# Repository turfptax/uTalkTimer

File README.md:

# uTalkTimer
uTalkTimer: An async ESPNOW-based MicroPython library for efficient discussion management in meetings, featuring speaker time tracking, speech queuing, and voting functionalities.

## Installation and Setup

Follow these instructions to set up the environment and install all required dependencies for the uTalkTimer project.

### Prerequisites

Before you begin, ensure you have MicroPython installed on your ESP32 device. You will also need to install `mpremote` to interact with your MicroPython device from your computer.

#### Installing mpremote

You can install `mpremote` using pip. Open your terminal and run:

```bash
pip install mpremote
```

### Installing Required Libraries

The project depends on the `aioespnow` and `ssd1306` libraries for asynchronous ESPNOW communication and OLED display management, respectively. Follow the steps below to install these libraries on your MicroPython device.

1. **Connect to Your MicroPython Device**:

   First, make sure to close any active IDE connections to the ESP32 micropython device:

   ```bash
   mpremote mip install aioespnow
   mpremote mip install ssd1306
   ```

2. **Verify Libraries**:

   Use thonny or another IDE to varify that the two files are stored in a 'lib' directory with the .mpy extension:

   ```bash
   lib
       aioespnow.mpy
       ssd1306.mpy
   ```
You should see `aioespnow.mpy` and `ssd1306.mpy` listed.

3. **Transfer the following files to your device**:

- boot.py
- freesans20.py (for larger font support)
- writer.py (required for rendering freesans20)

### Verifying the Installation

After installing the libraries, you can check if they are correctly placed by listing the files in the `/lib` directory on your device by trying to import the libraries:

```bash
import aioespnow
import ssd1306
```

## Running the Project

Once all prerequisites and required libraries are installed, you can upload power on the device:
Project runs on the boot.py at boot

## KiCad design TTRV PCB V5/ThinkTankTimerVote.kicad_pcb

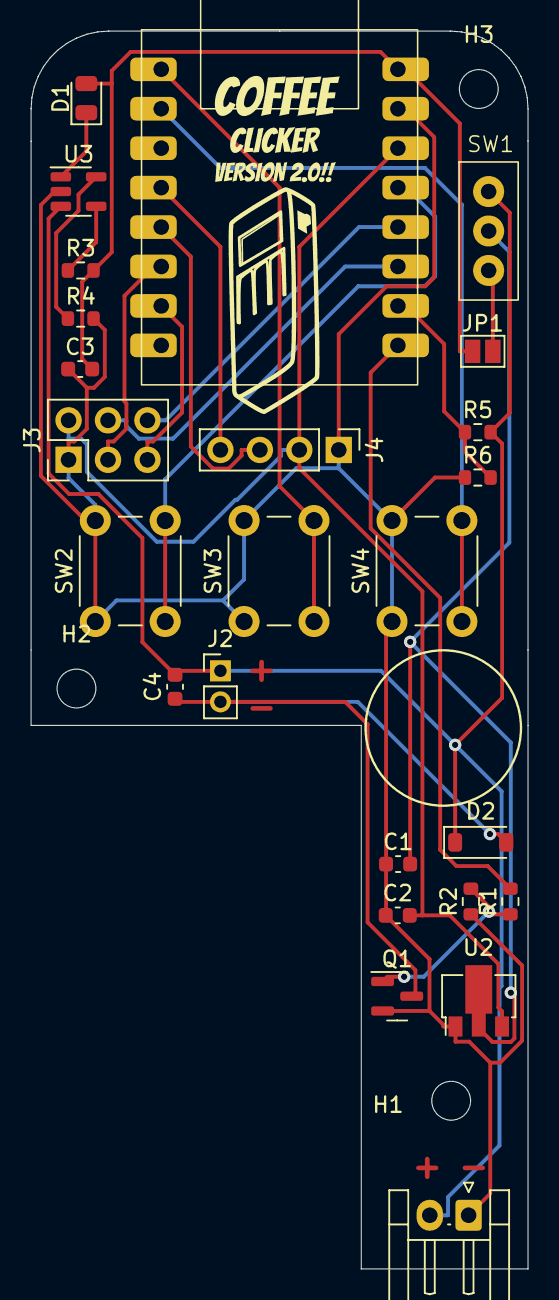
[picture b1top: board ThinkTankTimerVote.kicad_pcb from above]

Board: 2 copper layers, 32.0 x 79.7 mm, 28 parts (0 on the bottom side), 22 nets.

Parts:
C1, C2, C3: 2.2 uF; C_0603_1608Metric
C4: 100 uF; C_0603_1608Metric
D1: LED GREEN; LED_0805_2012Metric
D2: 1N4007; D_SOD-123
H1, H2, H3: MountingHole; MountingHole_2.5mm
J1: BattLeft; JST_EH_S2B-EH_1x02_P2.50mm_Horizontal
J2: Conn_01x02; PinHeader_1x02_P2.00mm_Vertical
J3: Conn_02x03_Odd_Even; PinHeader_2x03_P2.54mm_Vertical
J4: Conn_01x04; PinHeader_1x04_P2.54mm_Vertical
JP1: 5V Jump; SolderJumper-2_P1.3mm_Open_Pad1.0x1.5mm
Q1: IRLML2060; SOT-23
R1, R2, R5: 10k; R_0603_1608Metric
R3: 2k; R_0603_1608Metric
R4: 2.7k; R_0603_1608Metric
R6: 20k; R_0603_1608Metric
SW1: SW_DPDT_x2; Switch3Pin
SW2, SW3, SW4: SW_Push; SW_PUSH_6mm_H7.3mm
U1: ESP32-C3-Super Mini
U2: HT75xx-1-SOT89; SOT-89-3
U3: LTC4054ES5-4.2; TSOT-23-5

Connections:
+3V3: C2.2, J3.2, J4.2, U1.102 (3V3), U2.3 (VOUT)
+5V: C3.2, D1.2 (A), JP1.1 (A), R3.2, U1.100 (5V)
ADC1_BAT: R5.1, R6.2, U1.1 (GPIO1)
ADC2: J3.4, U1.2 (GPIO2)
ADC3: J3.6, U1.3 (GPIO3)
Batt+: C4.2, D2.1 (K), J1.2, J2.1, R5.2, SW1.1 (A), U3.3 (BAT)
GND: C1.1, C2.1, C3.1, J1.1, J3.1, J4.1, Q1.2 (S), R2.1, R4.2, R6.1, SW2.1, SW3.1, SW4.1, U1.101 (GND), U2.1 (GND), U3.2 (GND)
GPIO10: J3.3, U1.10 (GPIO10)
GPIO20: J3.5, U1.20 (GPIO20)
Left: SW2.2, U1.4 (GPIO4)
Middle: SW3.2, U1.5 (GPIO5)
MotSig: R1.2, U1.0 (GPIO0)
Motor-: C4.1, D2.2 (A), J2.2, Q1.3 (D)
unnamed: D1.1 (K), U3.1 (~CHRG)
unnamed: JP1.2 (B), SW1.3 (C)
unnamed: Q1.1 (G), R1.1, R2.2
unnamed: R4.1, U3.5 (PROG)
unnamed: R3.1, U3.4 (V_{CC})
Right: SW4.2, U1.6 (GPIO6)
SCL: J4.3, U1.9 (GPIO9)
SDA: J4.4, U1.8 (GPIO8)
VILDO: C1.2, SW1.2 (B), U2.2 (VIN)

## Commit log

2024-05-01 Create uTT.py
    Main upload of code
2024-05-01 Create boot.py
    Main program using async. Current uTT is the remote testing device.
2024-05-25 Update boot.py - added peers list
    Added Peers List
2024-05-25 Update boot.py - added timer
    Added timer tracking and boot time
    data stored in time_markers global.
2024-05-25 Update boot.py
    Configuring communication protocol for ad-hoc espnow between two devices.
2024-05-26 Update boot.py
    - Fixed interrupt debounce
    - Included writer.py and freesans20.py (larger fonts)
2024-05-26 Main Files
    PCB, STLs, and KiCad Files
2024-05-26 update file structure
2024-05-26 Main subitems
2024-05-27 major function adds
2024-05-29 Major Update
2024-05-29 Select Name function added
    Select name function added
2024-05-29 Queue Updated
    Adding queue logic
2024-05-29 Proper Talking Hand Off
2024-05-29 Updating Queue calculations
    Reducing some code overhead on network and recalculating queue
    :D
2024-05-29 Logging Function Added
    Adding logging functionality
2024-05-30 Update PCB
2024-05-30 Minor changes
2024-05-31 PCB Update
    Includes Artwork and Rough Draft KiCad Files
2024-05-31 PCB V 2.6.0
2024-06-05 PCB6 Micropython Pin Updates
    # Included battery level indicator
2024-06-07 Time Vote Fix
2024-07-01 v2.1 updates
